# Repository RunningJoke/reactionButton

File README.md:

# ReactPod

Reaction buzzers for training: an ESP32-C3 pod with an 18-LED ring and one big button. Several pods form
a **set**; one pod is the **central** and runs the game program, the others are **peripherals**. Programs
are JSON block graphs; the **Config App** builds, simulates and uploads them.

- **Config App:** https://runningjoke.github.io/reactionButton/ (PWA, works offline, demo pod built in)
- **User manual, coach guide, game modes** (en / de): [wiki](https://github.com/RunningJoke/reactionButton/wiki)
- **Developing:** [CLAUDE.md](CLAUDE.md) (map, commands, workflow, rules) and the specs in [docs/](docs/)

```sh
pio run -d firmware -e NewBoard -t upload      # flash over USB (first install, recovery); later versions: Config App, This set (ADR 0009)
pio run -d firmware -e NewBoard -t uploadfs    # flash the programs
python tools/reactpod_serial.py monitor        # log over USB
cd app && npm install && npm run dev           # http://localhost:5173
```

In VS Code open [reactpod.code-workspace](reactpod.code-workspace) so PlatformIO finds the firmware.

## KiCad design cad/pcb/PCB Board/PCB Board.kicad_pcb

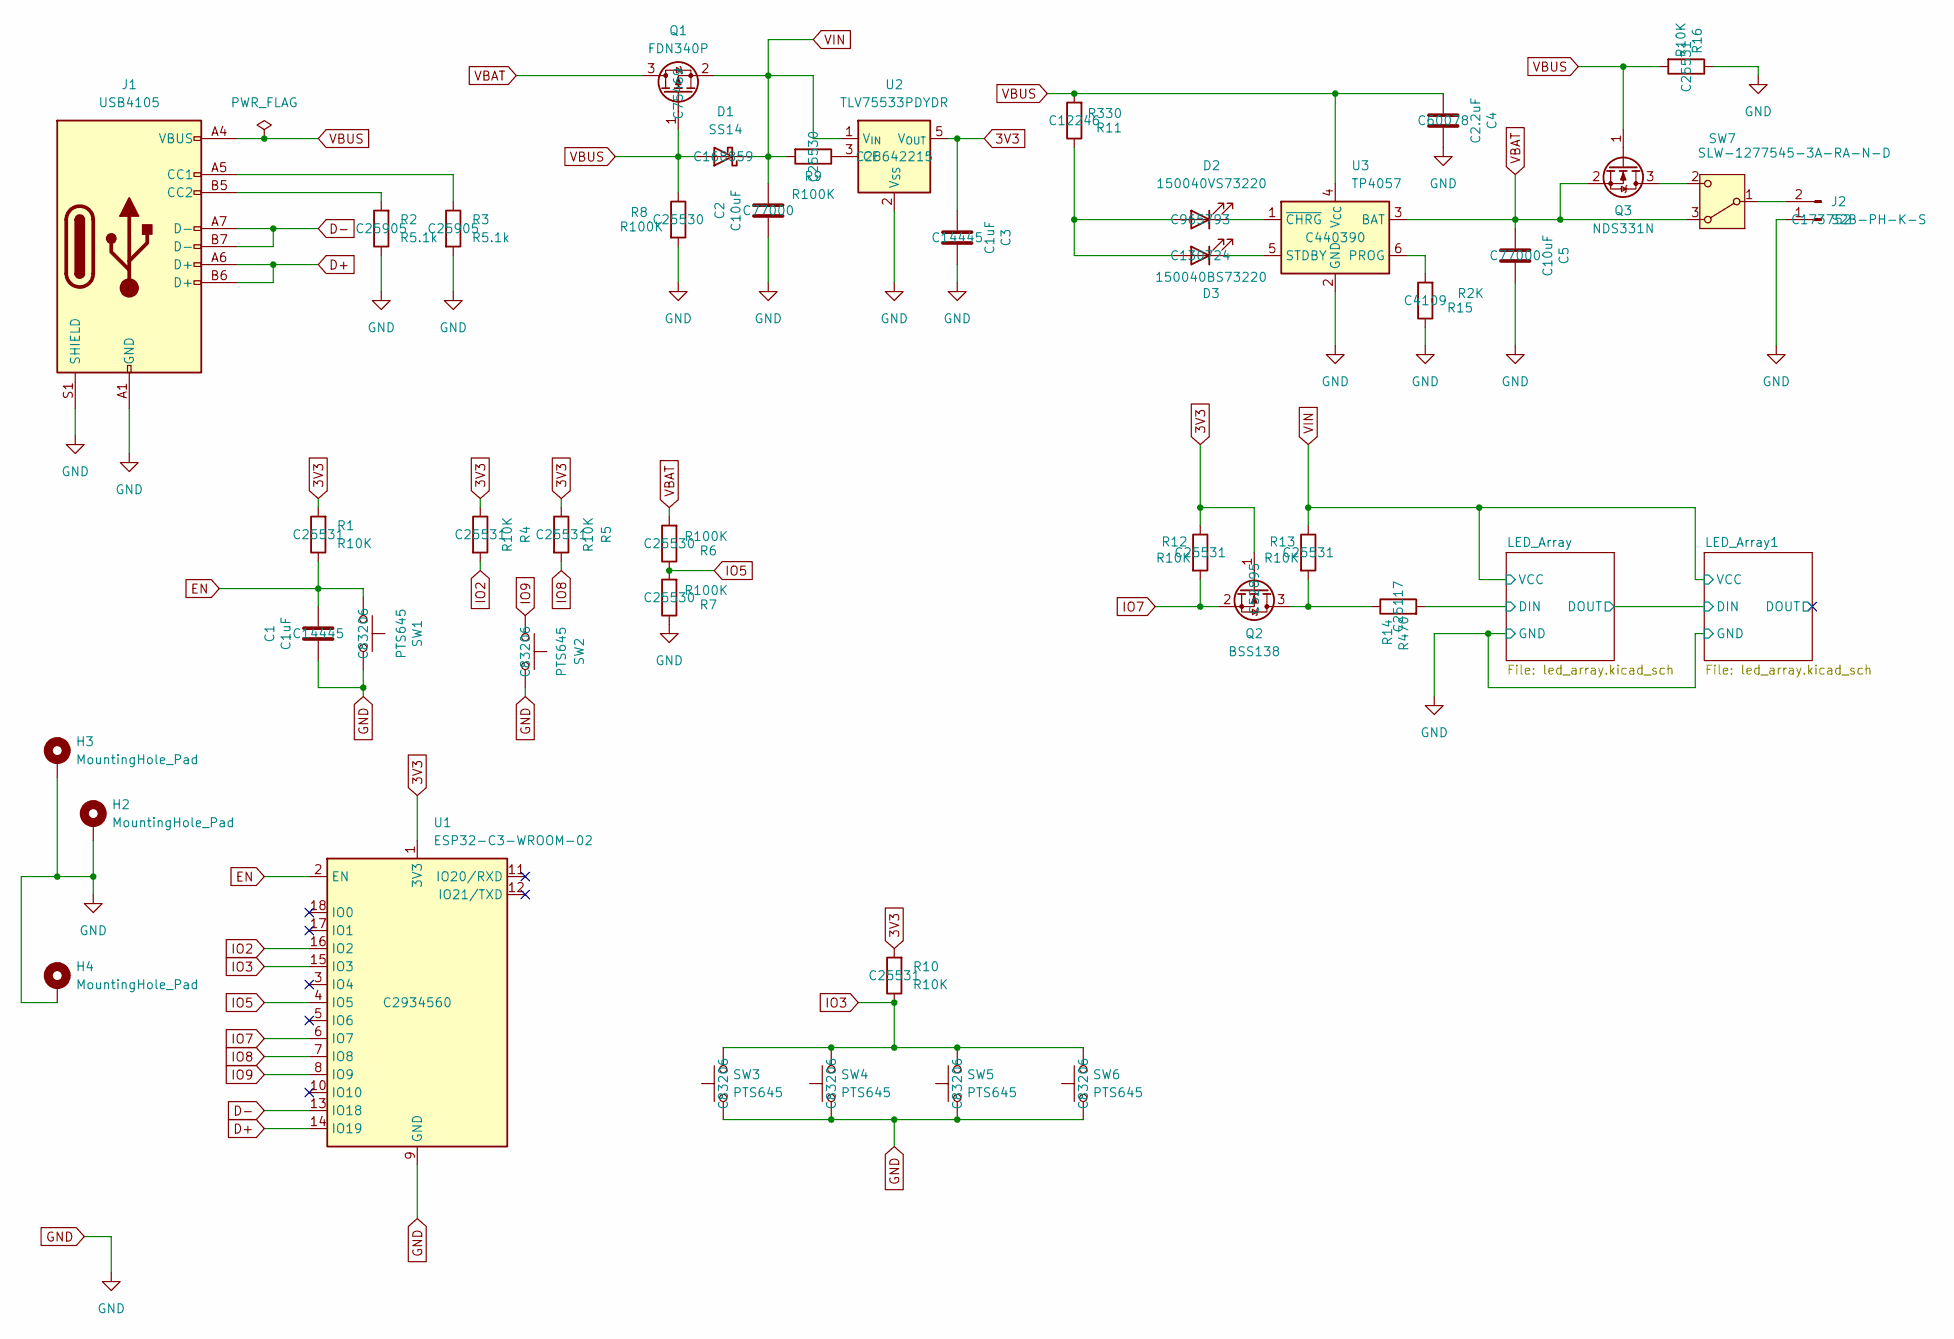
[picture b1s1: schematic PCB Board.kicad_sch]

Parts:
C1, C3: C1uF; C_0402_1005Metric; LCSC C14445
C2, C5: C10uF; C_0402_1005Metric; LCSC C77000
C4: C2.2uF; C_0402_1005Metric; LCSC C60078
D1: SS14; D_SMA; LCSC C168859
D2: 150040VS73220; LED_0402_1005Metric; LCSC C965793
D3: 150040BS73220; LED_0402_1005Metric; LCSC C130724
H2, H3, H4: MountingHole_Pad; MountingHole_3.2mm_M3_DIN965_Pad_TopBottom
J1: USB4105; USB_C_Receptacle_GCT_USB4105-xx-A_16P_TopMnt_Horizontal
J2: S2B-PH-K-S; JST_PH_S2B-PH-K_1x02_P2.00mm_Horizontal; LCSC C173752
Q1: FDN340P; SOT-23; LCSC C75469
Q2: BSS138; SOT-23; LCSC C52895
Q3: NDS331N; SOT-23
R1, R4, R5, R10, R12, R13, R16: R10K; R_0402_1005Metric; LCSC C25531
R2, R3: R5.1k; R_0402_1005Metric; LCSC C25905
R6, R7, R8, R9: R100K; R_0402_1005Metric; LCSC C25530
R11: R330; R_0402_1005Metric; LCSC C12246
R14: R470; R_0402_1005Metric; LCSC C25117
R15: R2K; R_0402_1005Metric; LCSC C4109
SW1, SW2, SW3, SW4, SW5, SW6: PTS645; SW_SPST_PTS645; LCSC C83206
SW7: SLW-1277545-3A-RA-N-D; SW_Slide_SPDT_Angled_CK_OS102011MA1Q; LCSC C431547
U1: ESP32-C3-WROOM-02; LCSC C2934560
U2: TLV75533PDYDR; SOT-23-5; LCSC C28642215
U3: TP4057; TSOT-23-6; LCSC C440390

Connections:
3V3: C3.1, Q2.1 (G), R1.2, R4.1, R5.1, R10.2, R12.1, U1.1 (3V3), U2.5 (V_{OUT})
D+: J1.A6 (D+), J1.B6 (D+), U1.14 (IO19)
D-: J1.A7 (D-), J1.B7 (D-), U1.13 (IO18)
EN: C1.2, R1.1, SW1.1, U1.2 (EN)
GND: C1.1, C2.1, C3.2, C4.2, C5.2, H2.1, H3.1, H4.1, J1.A1 (GND), J1.A12 (GND), J1.B1 (GND), J1.B12 (GND), J1.S1 (SHIELD), J2.1, R2.1, R3.2, R7.1, R8.2, R15.1, R16.1, SW1.2, SW2.1, SW3.1, SW4.1, SW5.1, SW6.1, U1.9 (GND), U1.19 (GND), U2.2 (V_{SS}), U3.2 (GND); also elsewhere on the board
IO2: R4.2, U1.16 (IO2)
IO3: R10.1, SW3.2, SW4.2, SW5.2, SW6.2, U1.15 (IO3)
IO5: R6.1, R7.2, U1.4 (IO5)
IO7: Q2.2 (S), R12.2, U1.6 (IO7)
IO8: R5.2, U1.7 (IO8)
IO9: SW2.2, U1.8 (IO9)
unnamed: D2.2 (A), D3.2 (A), R11.1
unnamed: D2.1 (K), U3.1 (~CHRG)
unnamed: D3.1 (K), U3.5 (STDBY)
unnamed: J1.A5 (CC1), R3.1
unnamed: J1.B5 (CC2), R2.2
unnamed: J2.2, SW7.1 (B)
unnamed: Q2.3 (D), R13.2, R14.1
unnamed: Q3.3 (D), SW7.2 (C)
unnamed: R9.1, U2.3 (CE)
unnamed: R15.2, U3.6 (PROG)
VBAT: C5.1, Q1.3 (D), Q3.2 (S), R6.2, SW7.3 (A), U3.3 (BAT)
VBUS: C4.1, D1.2 (A), J1.A4 (VBUS), J1.A9 (VBUS), J1.B4 (VBUS), J1.B9 (VBUS), Q1.1 (G), Q3.1 (G), R8.1, R11.2, R16.2, U3.4 (V_{CC})

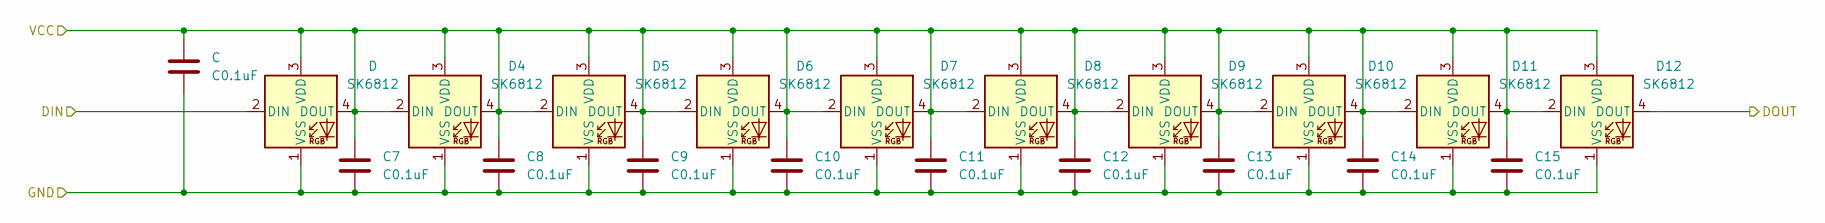
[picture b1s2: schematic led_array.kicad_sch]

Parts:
C, C7, C8, C9, C10, C11, C12, C13, C14, C15: C0.1uF; C_0402_1005Metric
D, D4, D5, D6, D7, D8, D9, D10, D11, D12: SK6812; LED_SK6812_PLCC4_5.0x5.0mm_P3.2mm

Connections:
/LED_Array/DOUT: D12.4 (DOUT); also elsewhere on the board
GND: C7.2, C8.2, C9.2, C10.2, C11.2, C12.2, C13.2, C14.2, C15.2, D4.1 (VSS), D5.1 (VSS), D6.1 (VSS), D7.1 (VSS), D8.1 (VSS), D9.1 (VSS), D10.1 (VSS), D11.1 (VSS), D12.1 (VSS); also elsewhere on the board

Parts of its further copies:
D13, D14, D15, D16, D17, D18, D19, D20, D21: SK6812; LED_SK6812_PLCC4_5.0x5.0mm_P3.2mm

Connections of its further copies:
/LED_Array1/DOUT: D21.4 (DOUT)
/LED_Array/DOUT: D13.2 (DIN); also elsewhere on the board
GND: D13.1 (VSS), D14.1 (VSS), D15.1 (VSS), D16.1 (VSS), D17.1 (VSS), D18.1 (VSS), D19.1 (VSS), D20.1 (VSS), D21.1 (VSS); also elsewhere on the board
unnamed: D14.4 (DOUT), D15.2 (DIN)
unnamed: D15.4 (DOUT), D16.2 (DIN)
unnamed: D16.4 (DOUT), D17.2 (DIN)
unnamed: D17.4 (DOUT), D18.2 (DIN)
unnamed: D18.4 (DOUT), D19.2 (DIN)
unnamed: D19.4 (DOUT), D20.2 (DIN)
unnamed: D20.4 (DOUT), D21.2 (DIN)

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
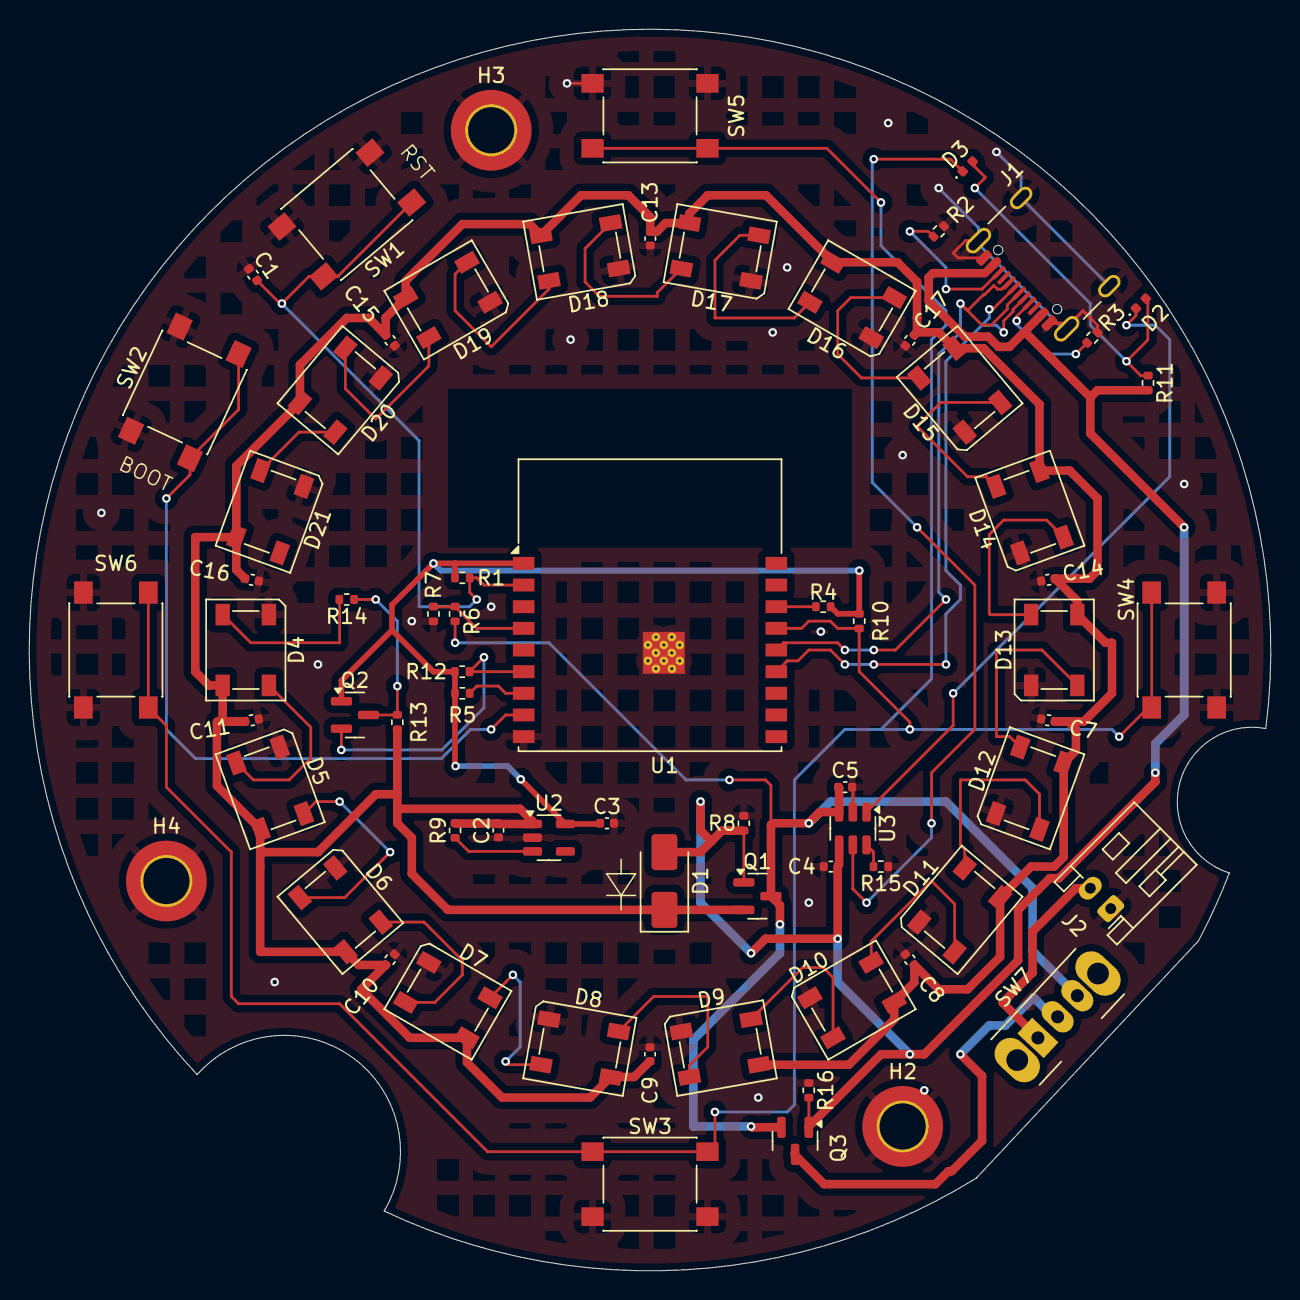
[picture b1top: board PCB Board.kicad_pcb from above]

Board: 2 copper layers, 86.0 x 86.0 mm, 70 parts (0 on the bottom side), 42 nets.

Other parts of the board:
C16, C17: C1uF; C_0402_1005Metric

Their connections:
GND: C16.2, C17.2; also elsewhere on the board

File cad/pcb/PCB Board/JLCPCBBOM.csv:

Comment;Designator;Footprint;LCSC Part Number;Footprint KiCad;Amount;Bezeichnung
ESP32-C3-WROOM-02-N4;U1;VFQFN-32-EP;C2934560;ESP32-C3-WROOM-02;1;ESP32-C3-WROOM-02
SMD tactile switch ;SW1,SW6,SW4,SW3,SW2,SW5;SPST;C83206;SW_SPST_PTS645;6;PTS645
C1uF 10V;C10,C14,C9,C16,C13,C7,C15,C3,C17,C1,C8,C11;0402;C14445;C_0402_1005Metric;12;C1uF
Resistor 5.1K;R3,R2;0402;C25905;R_0402_1005Metric;2;R5.1k
Resistor 10K;R10,R4,R5,R13,R1,R16,R12;0402;C25531;R_0402_1005Metric;7;R10K
RGB Diode with IC builtin;D19,D7,D6,D11,D5,D14,D8,D12,D20,D18,D9,D17,D21,D10,D4,D13,D16,D15;SMD5050;C114587;LED_SK6812_PLCC4_5.0x5.0mm_P3.2mm;18;SK6812
Rectifier Diode 10V;D1;SMA;C168859;D_SMA;1;SS14
Resistor 330;R11;0402;C12246;R_0402_1005Metric;1;R330
N-Channel MOSFET 200mA;Q2;SOT-23;C52895;SOT-23;1;BSS138
Resistor 100K;R6,R7,R9,R8;0402;C25530;R_0402_1005Metric;4;R100K
PH_S2B-PH 2 pin connector;J2;;C173752;JST_PH_S2B-PH-K_1x02_P2.00mm_Horizontal;1;S2B-PH-K-S
P-Channel MOSFET 2A 20V;Q1;SOT-23;C75469;SOT-23;1;FDN340P
Lithium-Ion BatteryManagement 600mA 5.5V;U3;TSOT-23-6;C440390;TSOT-23-6;1;TP4057
C10uF 10V;C2,C5;0402;C77000;C_0402_1005Metric;2;C10uF
Sliding switch ON-ON;SW7;SPDT;;SW_Slide_SPDT_Angled_CK_OS102011MA1Q;1;SLW-1277545-3A-RA-N-D
Linear Voltage regulator 3.3V 1A;U2;SOT-23-5;C28642215;SOT-23-5;1;TLV75533PDYDR
LED Blue 20mA;D3;0402;C130724;LED_0402_1005Metric;1;150040BS73220
USB-C connector;J1;SMD;;USB_C_Receptacle_GCT_USB4105-xx-A_16P_TopMnt_Horizontal;1;USB4105
Resistor 2K;R15;0402;C4109;R_0402_1005Metric;1;R2K
C2.2uF 10V;C4;0402;C60078;C_0402_1005Metric;1;C2.2uF
Resistor 470;R14;0402;C25117;R_0402_1005Metric;1;R470
LED Green 20mA;D2;0402;C965793;LED_0402_1005Metric;1;150040VS73220
N-Channel MOSFET 1.3A LogicLevel;Q3;SOT-23;;SOT-23;1;NDS331N

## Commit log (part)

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2024-02-25 save progress in initial development
2024-02-25 started pcb design
2024-03-03 started work on the pcb and cad data
2024-03-03 switched to neopixel library
2024-03-03 continued work on pcb
2024-03-23 updated pcbs
2024-03-23 updated container
2024-03-23 switched button pin and from NO to NC buttons
2024-03-30 save progress
2024-03-30 updated cad files
2024-03-30 updated gitignore
2024-03-31 [WIP] save progress
2024-03-31 fixed ble communication
2024-04-01 started reworking networking system
2024-04-01 [WIP] save progress
    currently not sending the data to the child nodes in alternating mode correctly. might be that the connection needs to be reestablished every time?
2024-04-06 fixed a crash at the end
2024-04-06 added deactivation support
2024-04-06 [SQUASH]childParentPodSystem
    commit 17b5b5690929541e9e3c602d57639d9a022262b0
    Author: Patrick Schwederski <schwederski@alli-go.de>
    Date: Sat Apr 6 08:08:58 2024 +0200
    added deactivation support
    commit b45540698f9067959a224b0df5a33577f7efcb2b
    Author: Patrick Schwederski <schwederski@alli-go.de>
2024-04-06 [SQUASH]cad-updates
    commit c678f14861f166de3e1cfd3d47229260420130a8
    Author: Patrick Schwederski <schwederski@alli-go.de>
    Date: Sat Mar 30 11:50:47 2024 +0100
    updated gitignore
    commit 5fc02eb109b8c870fff1fefb557780ef132b5a4d
    Author: Patrick Schwederski <schwederski@alli-go.de>
2024-04-06 added stl files
2024-04-07 moved to esp-idf and added watchdog support
2024-04-14 reworked the buzzer header for sturdier edge design
2024-12-21 updated 3d file
2025-03-07 updated pcb design schematic
    layouting missing. Also add on/off switch for battery (best solution with circumventing switch on charge
2025-03-07 remove in progress files accidentally commited
2025-03-16 [WIP] save changes
2025-03-16 updated schematic
2025-03-21 commit schematic as pdf
2025-03-22 updated with charging circuit
2025-03-26 updated pcb design
2025-03-26 commit cad design
2025-03-29 finished casing design
2025-04-03 fixed a wrong switch footprint
2025-04-03 commit first set of cad files
2025-04-06 save just reaction mode buzzer
2025-04-06 [WIP] updated casing files
2025-05-23 new buzzer layout
2025-05-23 updated cad data
2025-05-23 commit new 3d data files
2025-05-24 save new files
2025-05-24 adjusted tolerances
2025-05-25 another iteration of design
2025-05-25 added new board config
2025-05-25 [WIP]cleaned definition
2025-05-25 [WIP]save progress
2025-05-25 [WIP]add press button block
2025-05-30 added enterBlock and exitBlock methods for preparation/cleanup
2025-05-30 improved button block to handle more functionality
2025-05-30 added ble mesh configuration
2025-05-30 reworked for reaction buzzer functionality
2025-05-30 updated layout of case again
2025-05-30 removed unneeded librar<
2025-05-30 added animation capabilities
2025-07-02 [WIP] added peripheral class
2025-09-14 major updates
    new blocks
    new standard program
    bootup sequence
    VariableManager
2025-09-14 add new dependency
2025-09-14 added reaction mode
2025-09-14 store current progress
2025-09-14 add initial support for ble config
2025-09-15 fixed issue with unset max loop count
2025-09-15 updated casing
2025-09-21 cleaned up 3d casing data
2025-09-28 restructured code for easier readability
2025-09-29 added first draft of charging dock
2025-09-29 switched framework for support of up to 7 buzzers. And large rework
